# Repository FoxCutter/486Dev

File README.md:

# 486Dev
Repo for the 486 breadboard computer project

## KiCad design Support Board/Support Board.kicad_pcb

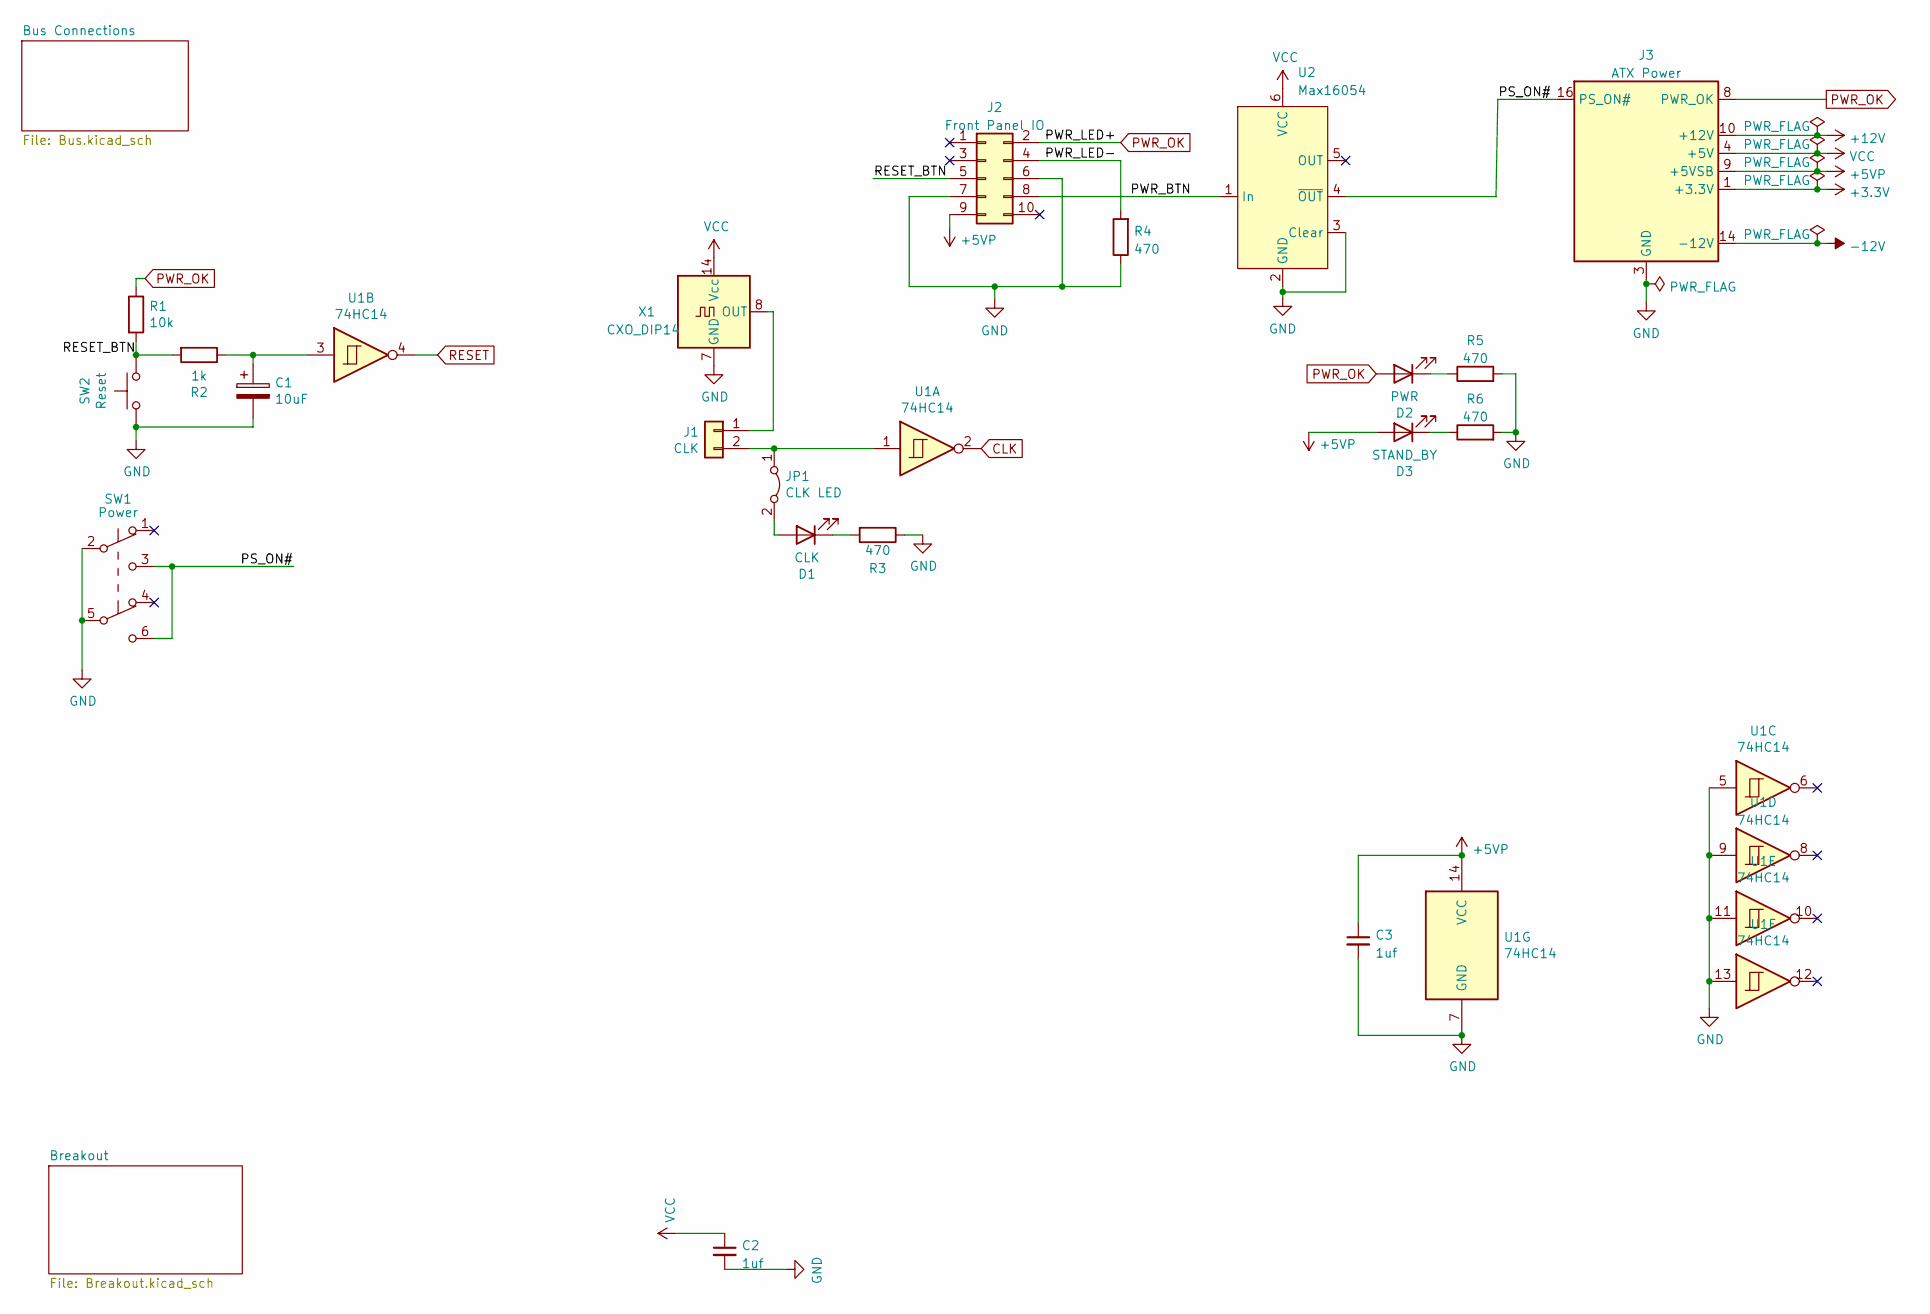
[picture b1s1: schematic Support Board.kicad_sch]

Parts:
C1: 10uF; CP_Radial_D5.0mm_P2.50mm
C2, C3: 1uf; C_0805_2012Metric_Pad1.18x1.45mm_HandSolder
D1: CLK; LED_0805_2012Metric_Pad1.15x1.40mm_HandSolder
D2: PWR; LED_0805_2012Metric_Pad1.15x1.40mm_HandSolder
D3: STAND_BY; LED_0805_2012Metric_Pad1.15x1.40mm_HandSolder
J1: CLK; PinHeader_1x02_P2.54mm_Vertical
J2: Front Panel IO; PinHeader_2x05_P2.54mm_Vertical
J3: ATX Power; Molex_Mini-Fit_Jr_5566-24A_2x12_P4.20mm_Vertical
JP1: CLK LED; PinHeader_1x02_P2.54mm_Vertical
R1: 10k; R_0805_2012Metric_Pad1.20x1.40mm_HandSolder
R2: 1k; R_0805_2012Metric_Pad1.20x1.40mm_HandSolder
R3, R4, R5, R6: 470; R_0805_2012Metric_Pad1.20x1.40mm_HandSolder
SW1: Power; 7mm x 7mm Tactile Switch
SW2: Reset; SW_PUSH_6mm
U1: 74HC14; SO-14_5.3x10.2mm_P1.27mm
U2: Max16054; TSOT-23-6
X1: CXO_DIP14; Oscillator_DIP-14

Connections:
+3.3V: J3.1 (+3.3V), J3.2 (+3.3V), J3.12 (+3.3V), J3.13 (+3.3V); also elsewhere on the board
+5VP: C3.1, D3.2 (A), J2.9, J3.9 (+5VSB), U1.14 (VCC); also elsewhere on the board
+12V: J3.10 (+12V), J3.11 (+12V); also elsewhere on the board
-12V: J3.14 (-12V); also elsewhere on the board
/PS_ON#: J3.16 (PS_ON#), SW1.3 (C), SW1.6 (C), U2.4 (~OUT)
/PWR_BTN: J2.8, U2.1 (In)
/PWR_LED-: J2.4, R4.2
/RESET_BTN: J2.5, R1.2, R2.2, SW2.2
CLK: U1.2; also elsewhere on the board
GND: C1.2, C2.2, C3.2, J2.6, J2.7, J3.3 (GND), J3.5 (GND), J3.7 (GND), J3.15 (GND), J3.17 (GND), J3.18 (GND), J3.19 (GND), J3.24 (GND), R3.1, R4.1, R5.2, R6.2, SW1.2 (B), SW1.5 (B), SW2.1, U1.5, U1.7 (GND), U1.9, U1.11, U1.13, U2.2 (GND), U2.3 (Clear), X1.7 (GND); also elsewhere on the board
unnamed: C1.1, R2.1, U1.3
unnamed: D1.1 (K), R3.2
unnamed: D1.2 (A), JP1.2 (B)
unnamed: D2.1 (K), R5.1
unnamed: D3.1 (K), R6.1
unnamed: J1.1, X1.8 (OUT)
unnamed: J1.2, JP1.1 (A), U1.1
PWR_OK: D2.2 (A), J2.2, J3.8 (PWR_OK), R1.1; also elsewhere on the board
RESET: U1.4; also elsewhere on the board
VCC: C2.1, J3.4 (+5V), J3.6 (+5V), J3.21 (+5V), J3.22 (+5V), J3.23 (+5V), U2.6 (VCC), X1.14 (Vcc); also elsewhere on the board

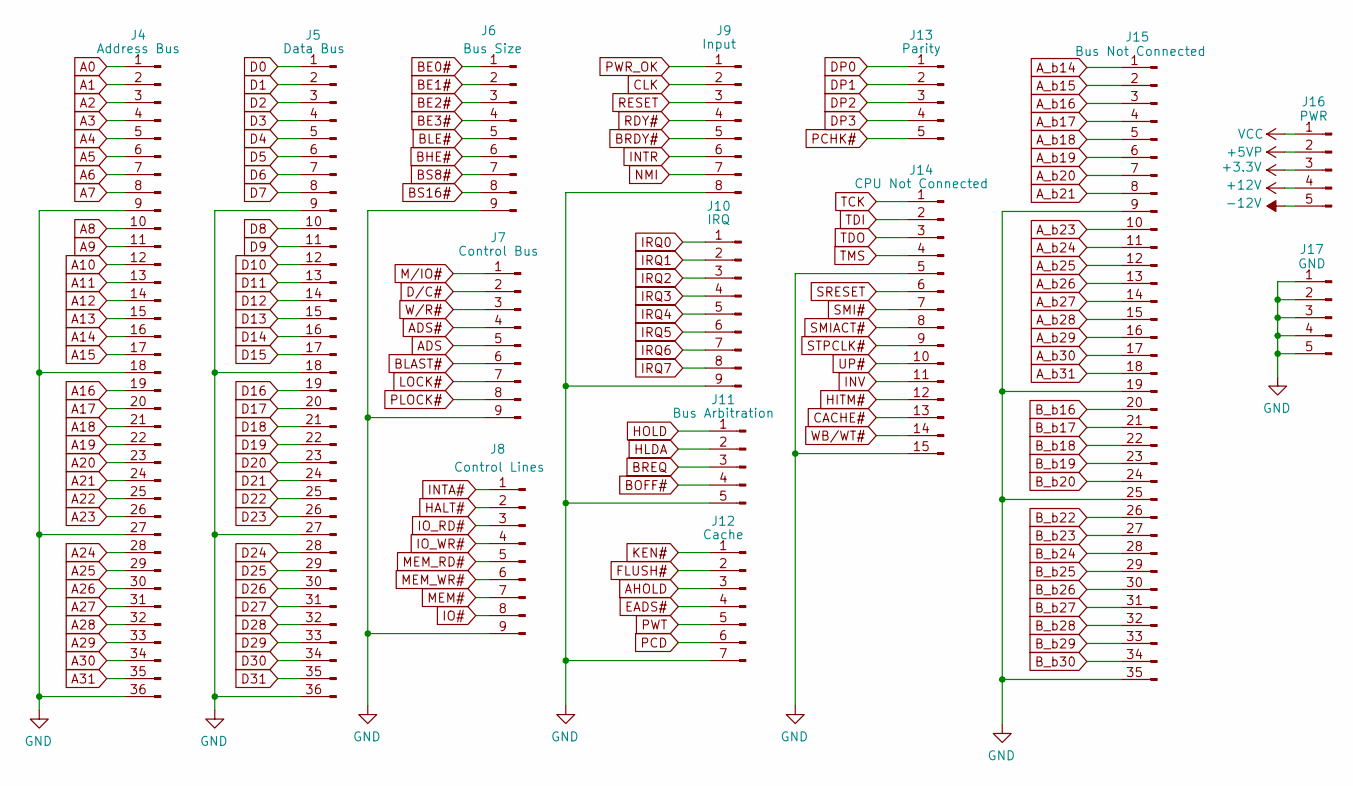
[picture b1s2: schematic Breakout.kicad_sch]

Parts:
J4: Address Bus; PinHeader_1x36_P2.54mm_Vertical
J5: Data Bus; PinHeader_1x36_P2.54mm_Vertical
J6: Bus Size; PinHeader_1x09_P2.54mm_Vertical
J7: Control Bus; PinHeader_1x09_P2.54mm_Vertical
J8: Control Lines; PinHeader_1x09_P2.54mm_Vertical
J9: Input; PinHeader_1x08_P2.54mm_Vertical
J10: IRQ; PinHeader_1x09_P2.54mm_Vertical
J11: Bus Arbitration; PinHeader_1x05_P2.54mm_Vertical
J12: Cache; PinHeader_1x07_P2.54mm_Vertical
J13: Parity; PinHeader_1x05_P2.54mm_Vertical
J14: CPU Not Connected; PinHeader_1x15_P2.54mm_Vertical
J15: Bus Not Connected; PinHeader_1x35_P2.54mm_Vertical
J16: PWR; PinHeader_1x05_P2.54mm_Vertical
J17: GND; PinHeader_1x05_P2.54mm_Vertical

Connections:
+3.3V: J16.3; also elsewhere on the board
+5VP: J16.2; also elsewhere on the board
+12V: J16.4; also elsewhere on the board
-12V: J16.5; also elsewhere on the board
A0: J4.1; also elsewhere on the board
A1: J4.2; also elsewhere on the board
A2: J4.3; also elsewhere on the board
A3: J4.4; also elsewhere on the board
A4: J4.5; also elsewhere on the board
A5: J4.6; also elsewhere on the board
A6: J4.7; also elsewhere on the board
A7: J4.8; also elsewhere on the board
A8: J4.10; also elsewhere on the board
A9: J4.11; also elsewhere on the board
A10: J4.12; also elsewhere on the board
A11: J4.13; also elsewhere on the board
A12: J4.14; also elsewhere on the board
A13: J4.15; also elsewhere on the board
A14: J4.16; also elsewhere on the board
A15: J4.17; also elsewhere on the board
A16: J4.19; also elsewhere on the board
A17: J4.20; also elsewhere on the board
A18: J4.21; also elsewhere on the board
A19: J4.22; also elsewhere on the board
A20: J4.23; also elsewhere on the board
A21: J4.24; also elsewhere on the board
A22: J4.25; also elsewhere on the board
A23: J4.26; also elsewhere on the board
A24: J4.28; also elsewhere on the board
A25: J4.29; also elsewhere on the board
A26: J4.30; also elsewhere on the board
A27: J4.31; also elsewhere on the board
A28: J4.32; also elsewhere on the board
A29: J4.33; also elsewhere on the board
A30: J4.34; also elsewhere on the board
A31: J4.35; also elsewhere on the board
ADS: J7.5; also elsewhere on the board
ADS#: J7.4; also elsewhere on the board
AHOLD: J12.3; also elsewhere on the board
A_b14: J15.1; also elsewhere on the board
A_b15: J15.2; also elsewhere on the board
A_b16: J15.3; also elsewhere on the board
A_b17: J15.4; also elsewhere on the board
A_b18: J15.5; also elsewhere on the board
A_b19: J15.6; also elsewhere on the board
A_b20: J15.7; also elsewhere on the board
A_b21: J15.8; also elsewhere on the board
A_b23: J15.10; also elsewhere on the board
A_b24: J15.11; also elsewhere on the board
A_b25: J15.12; also elsewhere on the board
A_b26: J15.13; also elsewhere on the board
A_b27: J15.14; also elsewhere on the board
A_b28: J15.15; also elsewhere on the board
A_b29: J15.16; also elsewhere on the board
A_b30: J15.17; also elsewhere on the board
A_b31: J15.18; also elsewhere on the board
BE0#: J6.1; also elsewhere on the board
BE1#: J6.2; also elsewhere on the board
BE2#: J6.3; also elsewhere on the board
BE3#: J6.4; also elsewhere on the board
BHE#: J6.6; also elsewhere on the board
BLAST#: J7.6; also elsewhere on the board
BLE#: J6.5; also elsewhere on the board
BOFF#: J11.4; also elsewhere on the board
BRDY#: J9.5; also elsewhere on the board
BREQ: J11.3; also elsewhere on the board
BS8#: J6.7; also elsewhere on the board
BS16#: J6.8; also elsewhere on the board
B_b16: J15.20; also elsewhere on the board
B_b17: J15.21; also elsewhere on the board
B_b18: J15.22; also elsewhere on the board
B_b19: J15.23; also elsewhere on the board
B_b20: J15.24; also elsewhere on the board
B_b22: J15.26; also elsewhere on the board
B_b23: J15.27; also elsewhere on the board
B_b24: J15.28; also elsewhere on the board
B_b25: J15.29; also elsewhere on the board
B_b26: J15.30; also elsewhere on the board
B_b27: J15.31; also elsewhere on the board
B_b28: J15.32; also elsewhere on the board
B_b29: J15.33; also elsewhere on the board
B_b30: J15.34; also elsewhere on the board
CACHE#: J14.13; also elsewhere on the board
CLK: J9.2; also elsewhere on the board
D0: J5.1; also elsewhere on the board
D1: J5.2; also elsewhere on the board
D2: J5.3; also elsewhere on the board
D3: J5.4; also elsewhere on the board
D4: J5.5; also elsewhere on the board
D5: J5.6; also elsewhere on the board
D6: J5.7; also elsewhere on the board
D7: J5.8; also elsewhere on the board
D8: J5.10; also elsewhere on the board
D9: J5.11; also elsewhere on the board
D10: J5.12; also elsewhere on the board
D11: J5.13; also elsewhere on the board
D12: J5.14; also elsewhere on the board
D13: J5.15; also elsewhere on the board
D14: J5.16; also elsewhere on the board
D15: J5.17; also elsewhere on the board
D16: J5.19; also elsewhere on the board
D17: J5.20; also elsewhere on the board
D18: J5.21; also elsewhere on the board
D19: J5.22; also elsewhere on the board
D20: J5.23; also elsewhere on the board
D21: J5.24; also elsewhere on the board
D22: J5.25; also elsewhere on the board
D23: J5.26; also elsewhere on the board
D24: J5.28; also elsewhere on the board
D25: J5.29; also elsewhere on the board
D26: J5.30; also elsewhere on the board
D27: J5.31; also elsewhere on the board
D28: J5.32; also elsewhere on the board
D29: J5.33; also elsewhere on the board
D30: J5.34; also elsewhere on the board
D31: J5.35; also elsewhere on the board
DP0: J13.1; also elsewhere on the board
DP1: J13.2; also elsewhere on the board
DP2: J13.3; also elsewhere on the board
DP3: J13.4; also elsewhere on the board
D/C#: J7.2; also elsewhere on the board
EADS#: J12.4; also elsewhere on the board
FLUSH#: J12.2; also elsewhere on the board
GND: J4.9, J4.18, J4.27, J4.36, J5.9, J5.18, J5.27, J5.36, J6.9, J7.9, J8.9, J9.8, J10.9, J11.5, J12.7, J14.5, J14.15, J15.9, J15.19, J15.25, J15.35, J17.1, J17.2, J17.3, J17.4, J17.5; also elsewhere on the board
HALT#: J8.2; also elsewhere on the board
HITM#: J14.12; also elsewhere on the board
HLDA: J11.2; also elsewhere on the board
HOLD: J11.1; also elsewhere on the board
INTA#: J8.1; also elsewhere on the board
INTR: J9.6; also elsewhere on the board
INV: J14.11; also elsewhere on the board
IO#: J8.8; also elsewhere on the board
IO_RD#: J8.3; also elsewhere on the board
IO_WR#: J8.4; also elsewhere on the board
IRQ0: J10.1; also elsewhere on the board
IRQ1: J10.2; also elsewhere on the board
IRQ2: J10.3; also elsewhere on the board
IRQ3: J10.4; also elsewhere on the board
IRQ4: J10.5; also elsewhere on the board
IRQ5: J10.6; also elsewhere on the board
IRQ6: J10.7; also elsewhere on the board
IRQ7: J10.8; also elsewhere on the board
KEN#: J12.1; also elsewhere on the board
LOCK#: J7.7; also elsewhere on the board
MEM#: J8.7; also elsewhere on the board
MEM_RD#: J8.5; also elsewhere on the board
MEM_WR#: J8.6; also elsewhere on the board
M/IO#: J7.1; also elsewhere on the board
NMI: J9.7; also elsewhere on the board
PCD: J12.6; also elsewhere on the board
PCHK#: J13.5; also elsewhere on the board
PLOCK#: J7.8; also elsewhere on the board
PWR_OK: J9.1; also elsewhere on the board
PWT: J12.5; also elsewhere on the board
RDY#: J9.4; also elsewhere on the board
RESET: J9.3; also elsewhere on the board
SMI#: J14.7; also elsewhere on the board
SMIACT#: J14.8; also elsewhere on the board
SRESET: J14.6; also elsewhere on the board
STPCLK#: J14.9; also elsewhere on the board
TCK: J14.1; also elsewhere on the board
TDI: J14.2; also elsewhere on the board
TDO: J14.3; also elsewhere on the board
TMS: J14.4; also elsewhere on the board
UP#: J14.10; also elsewhere on the board
VCC: J16.1; also elsewhere on the board
WB/WT#: J14.14; also elsewhere on the board
W/R#: J7.3; also elsewhere on the board

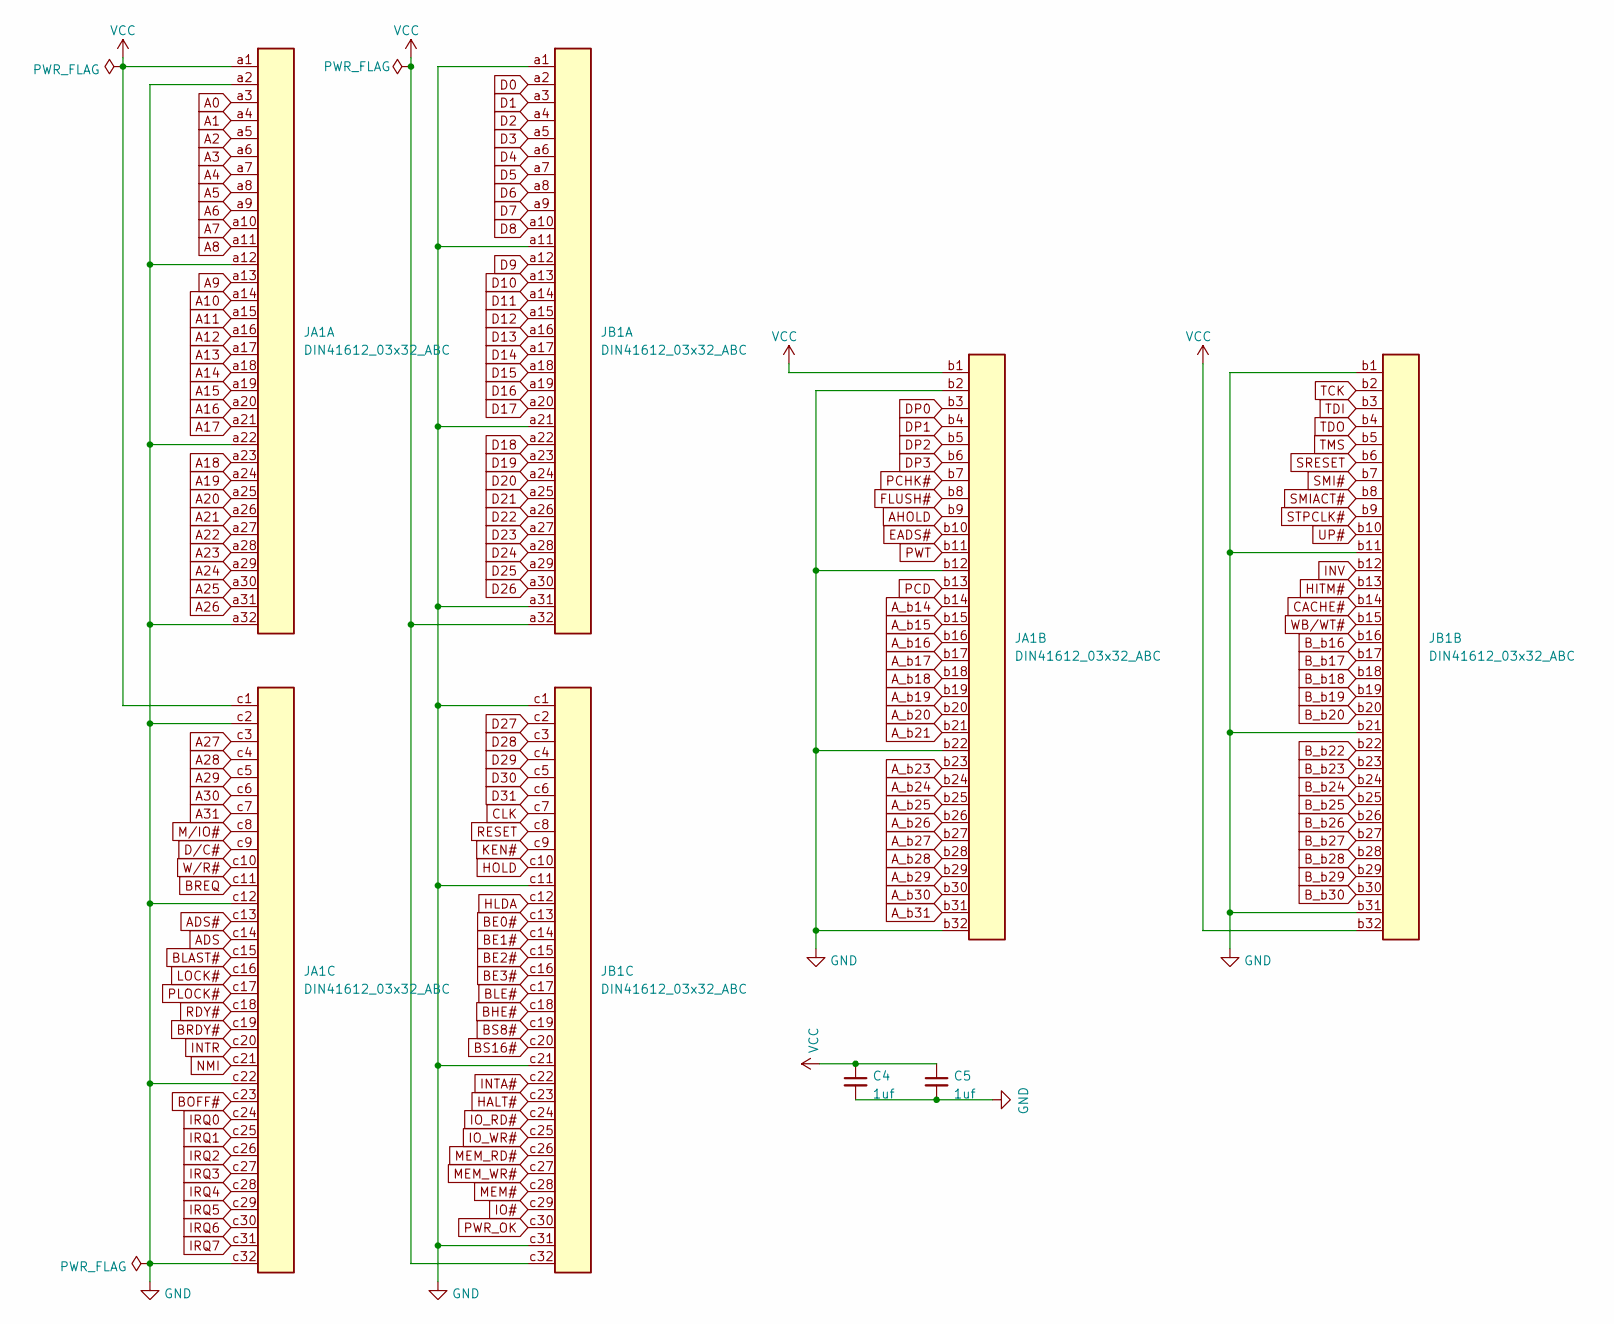
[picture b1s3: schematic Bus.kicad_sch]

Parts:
C4, C5: 1uf; C_0805_2012Metric_Pad1.18x1.45mm_HandSolder
JA1: DIN41612_03x32_ABC; DIN41612_R_3x32_Male_Horizontal_THT
JB1: DIN41612_03x32_ABC; DIN41612_R_3x32_Male_Horizontal_THT

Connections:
A0: JA1.a3; also elsewhere on the board
A1: JA1.a4; also elsewhere on the board
A2: JA1.a5; also elsewhere on the board
A3: JA1.a6; also elsewhere on the board
A4: JA1.a7; also elsewhere on the board
A5: JA1.a8; also elsewhere on the board
A6: JA1.a9; also elsewhere on the board
A7: JA1.a10; also elsewhere on the board
A8: JA1.a11; also elsewhere on the board
A9: JA1.a13; also elsewhere on the board
A10: JA1.a14; also elsewhere on the board
A11: JA1.a15; also elsewhere on the board
A12: JA1.a16; also elsewhere on the board
A13: JA1.a17; also elsewhere on the board
A14: JA1.a18; also elsewhere on the board
A15: JA1.a19; also elsewhere on the board
A16: JA1.a20; also elsewhere on the board
A17: JA1.a21; also elsewhere on the board
A18: JA1.a23; also elsewhere on the board
A19: JA1.a24; also elsewhere on the board
A20: JA1.a25; also elsewhere on the board
A21: JA1.a26; also elsewhere on the board
A22: JA1.a27; also elsewhere on the board
A23: JA1.a28; also elsewhere on the board
A24: JA1.a29; also elsewhere on the board
A25: JA1.a30; also elsewhere on the board
A26: JA1.a31; also elsewhere on the board
A27: JA1.c3; also elsewhere on the board
A28: JA1.c4; also elsewhere on the board
A29: JA1.c5; also elsewhere on the board
A30: JA1.c6; also elsewhere on the board
A31: JA1.c7; also elsewhere on the board
ADS: JA1.c14; also elsewhere on the board
ADS#: JA1.c13; also elsewhere on the board
AHOLD: JA1.b9; also elsewhere on the board
A_b14: JA1.b14; also elsewhere on the board
A_b15: JA1.b15; also elsewhere on the board
A_b16: JA1.b16; also elsewhere on the board
A_b17: JA1.b17; also elsewhere on the board
A_b18: JA1.b18; also elsewhere on the board
A_b19: JA1.b19; also elsewhere on the board
A_b20: JA1.b20; also elsewhere on the board
A_b21: JA1.b21; also elsewhere on the board
A_b23: JA1.b23; also elsewhere on the board
A_b24: JA1.b24; also elsewhere on the board
A_b25: JA1.b25; also elsewhere on the board
A_b26: JA1.b26; also elsewhere on the board
A_b27: JA1.b27; also elsewhere on the board
A_b28: JA1.b28; also elsewhere on the board
A_b29: JA1.b29; also elsewhere on the board
A_b30: JA1.b30; also elsewhere on the board
A_b31: JA1.b31; also elsewhere on the board
BE0#: JB1.c13; also elsewhere on the board
BE1#: JB1.c14; also elsewhere on the board
BE2#: JB1.c15; also elsewhere on the board
BE3#: JB1.c16; also elsewhere on the board
BHE#: JB1.c18; also elsewhere on the board
BLAST#: JA1.c15; also elsewhere on the board
BLE#: JB1.c17; also elsewhere on the board
BOFF#: JA1.c23; also elsewhere on the board
BRDY#: JA1.c19; also elsewhere on the board
BREQ: JA1.c11; also elsewhere on the board
BS8#: JB1.c19; also elsewhere on the board
BS16#: JB1.c20; also elsewhere on the board
B_b16: JB1.b16; also elsewhere on the board
B_b17: JB1.b17; also elsewhere on the board
B_b18: JB1.b18; also elsewhere on the board
B_b19: JB1.b19; also elsewhere on the board
B_b20: JB1.b20; also elsewhere on the board
B_b22: JB1.b22; also elsewhere on the board
B_b23: JB1.b23; also elsewhere on the board
B_b24: JB1.b24; also elsewhere on the board
B_b25: JB1.b25; also elsewhere on the board
B_b26: JB1.b26; also elsewhere on the board
B_b27: JB1.b27; also elsewhere on the board
B_b28: JB1.b28; also elsewhere on the board
B_b29: JB1.b29; also elsewhere on the board
B_b30: JB1.b30; also elsewhere on the board
CACHE#: JB1.b14; also elsewhere on the board
CLK: JB1.c7; also elsewhere on the board
D0: JB1.a2; also elsewhere on the board
D1: JB1.a3; also elsewhere on the board
D2: JB1.a4; also elsewhere on the board
D3: JB1.a5; also elsewhere on the board
D4: JB1.a6; also elsewhere on the board
D5: JB1.a7; also elsewhere on the board
D6: JB1.a8; also elsewhere on the board
D7: JB1.a9; also elsewhere on the board
D8: JB1.a10; also elsewhere on the board
D9: JB1.a12; also elsewhere on the board
D10: JB1.a13; also elsewhere on the board
D11: JB1.a14; also elsewhere on the board
D12: JB1.a15; also elsewhere on the board
D13: JB1.a16; also elsewhere on the board
D14: JB1.a17; also elsewhere on the board
D15: JB1.a18; also elsewhere on the board
D16: JB1.a19; also elsewhere on the board
D17: JB1.a20; also elsewhere on the board
D18: JB1.a22; also elsewhere on the board
D19: JB1.a23; also elsewhere on the board
D20: JB1.a24; also elsewhere on the board
D21: JB1.a25; also elsewhere on the board
D22: JB1.a26; also elsewhere on the board
D23: JB1.a27; also elsewhere on the board
D24: JB1.a28; also elsewhere on the board
D25: JB1.a29; also elsewhere on the board
D26: JB1.a30; also elsewhere on the board
D27: JB1.c2; also elsewhere on the board
D28: JB1.c3; also elsewhere on the board
D29: JB1.c4; also elsewhere on the board
D30: JB1.c5; also elsewhere on the board
D31: JB1.c6; also elsewhere on the board
DP0: JA1.b3; also elsewhere on the board
DP1: JA1.b4; also elsewhere on the board
DP2: JA1.b5; also elsewhere on the board
DP3: JA1.b6; also elsewhere on the board
D/C#: JA1.c9; also elsewhere on the board
EADS#: JA1.b10; also elsewhere on the board
FLUSH#: JA1.b8; also elsewhere on the board
GND: C4.2, C5.2, JA1.a2, JA1.a12, JA1.a22, JA1.a32, JA1.b2, JA1.b12, JA1.b22, JA1.b32, JA1.c2, JA1.c12, JA1.c22, JA1.c32, JB1.a1, JB1.a11, JB1.a21, JB1.a31, JB1.b1, JB1.b11, JB1.b21, JB1.b31, JB1.c1, JB1.c11, JB1.c21, JB1.c31; also elsewhere on the board
HALT#: JB1.c23; also elsewhere on the board
HITM#: JB1.b13; also elsewhere on the board
HLDA: JB1.c12; also elsewhere on the board
HOLD: JB1.c10; also elsewhere on the board
INTA#: JB1.c22; also elsewhere on the board
INTR: JA1.c20; also elsewhere on the board
INV: JB1.b12; also elsewhere on the board
IO#: JB1.c29; also elsewhere on the board
IO_RD#: JB1.c24; also elsewhere on the board
IO_WR#: JB1.c25; also elsewhere on the board
IRQ0: JA1.c24; also elsewhere on the board
IRQ1: JA1.c25; also elsewhere on the board
IRQ2: JA1.c26; also elsewhere on the board
IRQ3: JA1.c27; also elsewhere on the board
IRQ4: JA1.c28; also elsewhere on the board
IRQ5: JA1.c29; also elsewhere on the board
IRQ6: JA1.c30; also elsewhere on the board
IRQ7: JA1.c31; also elsewhere on the board
KEN#: JB1.c9; also elsewhere on the board
LOCK#: JA1.c16; also elsewhere on the board
MEM#: JB1.c28; also elsewhere on the board
MEM_RD#: JB1.c26; also elsewhere on the board
MEM_WR#: JB1.c27; also elsewhere on the board
M/IO#: JA1.c8; also elsewhere on the board
NMI: JA1.c21; also elsewhere on the board
PCD: JA1.b13; also elsewhere on the board
PCHK#: JA1.b7; also elsewhere on the board
PLOCK#: JA1.c17; also elsewhere on the board
PWR_OK: JB1.c30; also elsewhere on the board
PWT: JA1.b11; also elsewhere on the board
RDY#: JA1.c18; also elsewhere on the board
RESET: JB1.c8; also elsewhere on the board
SMI#: JB1.b7; also elsewhere on the board
SMIACT#: JB1.b8; also elsewhere on the board
SRESET: JB1.b6; also elsewhere on the board
STPCLK#: JB1.b9; also elsewhere on the board
TCK: JB1.b2; also elsewhere on the board
TDI: JB1.b3; also elsewhere on the board
TDO: JB1.b4; also elsewhere on the board
TMS: JB1.b5; also elsewhere on the board
UP#: JB1.b10; also elsewhere on the board
VCC: C4.1, C5.1, JA1.a1, JA1.b1, JA1.c1, JB1.a32, JB1.b32, JB1.c32; also elsewhere on the board
WB/WT#: JB1.b15; also elsewhere on the board
W/R#: JA1.c10; also elsewhere on the board

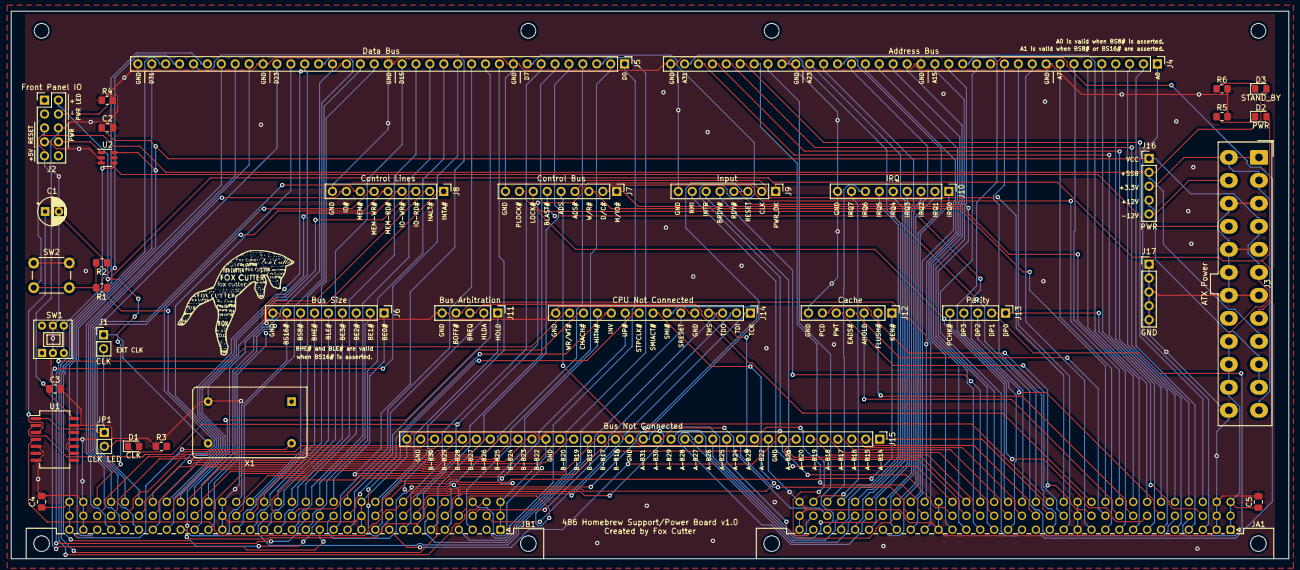
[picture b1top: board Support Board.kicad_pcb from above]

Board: 2 copper layers, 233.3 x 100.0 mm, 43 parts (0 on the bottom side), 179 nets.

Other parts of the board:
REF1, REF2, REF3, REF4: MountingHole_2.7mm_M2.5_ISO7380

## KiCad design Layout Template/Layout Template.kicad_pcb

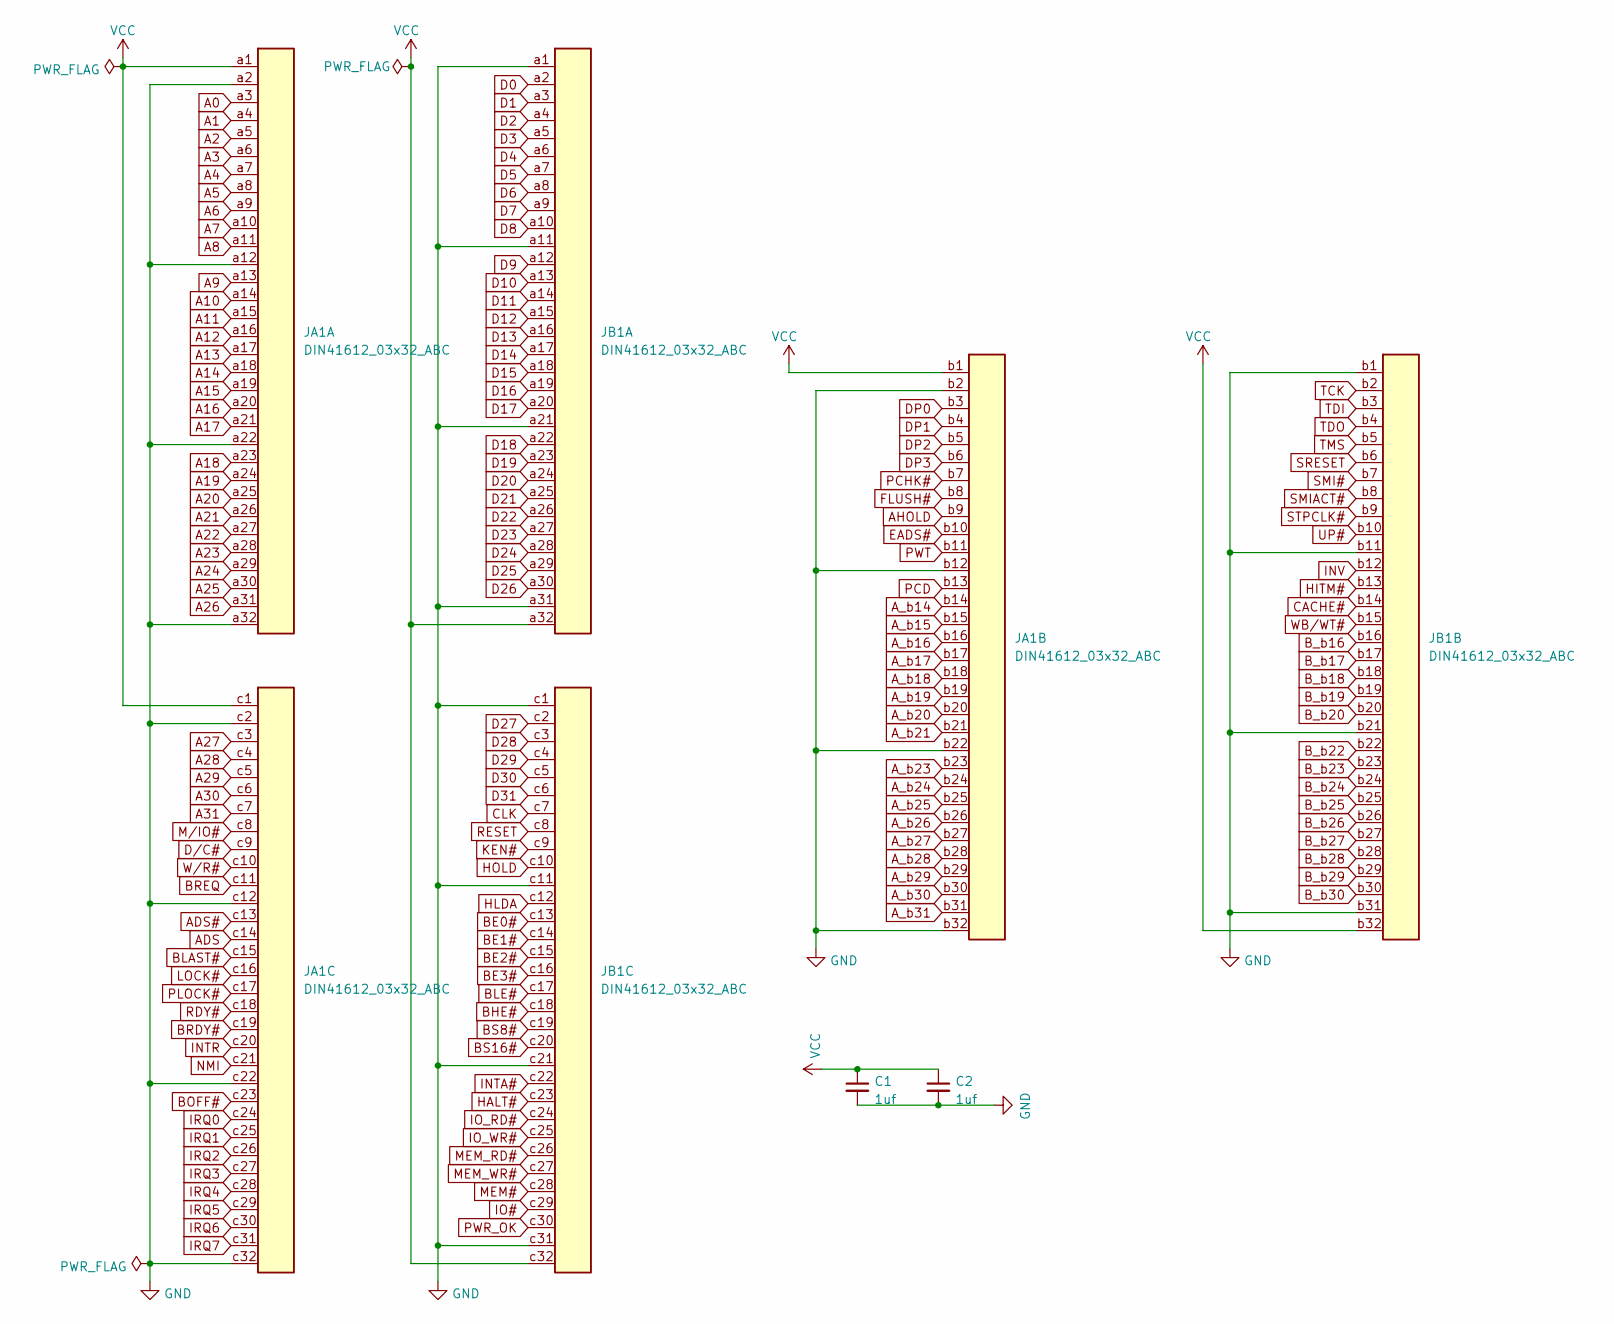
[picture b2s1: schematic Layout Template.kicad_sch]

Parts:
C1, C2: 1uf; C_Disc_D4.7mm_W2.5mm_P5.00mm
JA1: DIN41612_03x32_ABC; DIN41612_R_3x32_Male_Horizontal_THT
JB1: DIN41612_03x32_ABC; DIN41612_R_3x32_Male_Horizontal_THT

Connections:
A0: JA1.a3
A1: JA1.a4
A2: JA1.a5
A3: JA1.a6
A4: JA1.a7
A5: JA1.a8
A6: JA1.a9
A7: JA1.a10
A8: JA1.a11
A9: JA1.a13
A10: JA1.a14
A11: JA1.a15
A12: JA1.a16
A13: JA1.a17
A14: JA1.a18
A15: JA1.a19
A16: JA1.a20
A17: JA1.a21
A18: JA1.a23
A19: JA1.a24
A20: JA1.a25
A21: JA1.a26
A22: JA1.a27
A23: JA1.a28
A24: JA1.a29
A25: JA1.a30
A26: JA1.a31
A27: JA1.c3
A28: JA1.c4
A29: JA1.c5
A30: JA1.c6
A31: JA1.c7
ADS: JA1.c14
ADS#: JA1.c13
AHOLD: JA1.b9
A_b14: JA1.b14
A_b15: JA1.b15
A_b16: JA1.b16
A_b17: JA1.b17
A_b18: JA1.b18
A_b19: JA1.b19
A_b20: JA1.b20
A_b21: JA1.b21
A_b23: JA1.b23
A_b24: JA1.b24
A_b25: JA1.b25
A_b26: JA1.b26
A_b27: JA1.b27
A_b28: JA1.b28
A_b29: JA1.b29
A_b30: JA1.b30
A_b31: JA1.b31
BE0#: JB1.c13
BE1#: JB1.c14
BE2#: JB1.c15
BE3#: JB1.c16
BHE#: JB1.c18
BLAST#: JA1.c15
BLE#: JB1.c17
BOFF#: JA1.c23
BRDY#: JA1.c19
BREQ: JA1.c11
BS8#: JB1.c19
BS16#: JB1.c20
B_b16: JB1.b16
B_b17: JB1.b17
B_b18: JB1.b18
B_b19: JB1.b19
B_b20: JB1.b20
B_b22: JB1.b22
B_b23: JB1.b23
B_b24: JB1.b24
B_b25: JB1.b25
B_b26: JB1.b26
B_b27: JB1.b27
B_b28: JB1.b28
B_b29: JB1.b29
B_b30: JB1.b30
CACHE#: JB1.b14
CLK: JB1.c7
D0: JB1.a2
D1: JB1.a3
D2: JB1.a4
D3: JB1.a5
D4: JB1.a6
D5: JB1.a7
D6: JB1.a8
D7: JB1.a9
D8: JB1.a10
D9: JB1.a12
D10: JB1.a13
D11: JB1.a14
D12: JB1.a15
D13: JB1.a16
D14: JB1.a17
D15: JB1.a18
D16: JB1.a19
D17: JB1.a20
D18: JB1.a22
D19: JB1.a23
D20: JB1.a24
D21: JB1.a25
D22: JB1.a26
D23: JB1.a27
D24: JB1.a28
D25: JB1.a29
D26: JB1.a30
D27: JB1.c2
D28: JB1.c3
D29: JB1.c4
D30: JB1.c5
D31: JB1.c6
DP0: JA1.b3
DP1: JA1.b4
DP2: JA1.b5
DP3: JA1.b6
D/C#: JA1.c9
EADS#: JA1.b10
FLUSH#: JA1.b8
GND: C1.2, C2.2, JA1.a2, JA1.a12, JA1.a22, JA1.a32, JA1.b2, JA1.b12, JA1.b22, JA1.b32, JA1.c2, JA1.c12, JA1.c22, JA1.c32, JB1.a1, JB1.a11, JB1.a21, JB1.a31, JB1.b1, JB1.b11, JB1.b21, JB1.b31, JB1.c1, JB1.c11, JB1.c21, JB1.c31
HALT#: JB1.c23
HITM#: JB1.b13
HLDA: JB1.c12
HOLD: JB1.c10
INTA#: JB1.c22
INTR: JA1.c20
INV: JB1.b12
IO#: JB1.c29
IO_RD#: JB1.c24
IO_WR#: JB1.c25
IRQ0: JA1.c24
IRQ1: JA1.c25
IRQ2: JA1.c26
IRQ3: JA1.c27
IRQ4: JA1.c28
IRQ5: JA1.c29
IRQ6: JA1.c30
IRQ7: JA1.c31
KEN#: JB1.c9
LOCK#: JA1.c16
MEM#: JB1.c28
MEM_RD#: JB1.c26
MEM_WR#: JB1.c27
M/IO#: JA1.c8
NMI: JA1.c21
PCD: JA1.b13
PCHK#: JA1.b7
PLOCK#: JA1.c17
PWR_OK: JB1.c30
PWT: JA1.b11
RDY#: JA1.c18
RESET: JB1.c8
SMI#: JB1.b7
SMIACT#: JB1.b8
SRESET: JB1.b6
STPCLK#: JB1.b9
TCK: JB1.b2
TDI: JB1.b3
TDO: JB1.b4
TMS: JB1.b5
UP#: JB1.b10
VCC: C1.1, C2.1, JA1.a1, JA1.b1, JA1.c1, JB1.a32, JB1.b32, JB1.c32
WB/WT#: JB1.b15
W/R#: JA1.c10

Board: 2 copper layers, 8 parts (0 on the bottom side), 2 nets, no tracks yet.

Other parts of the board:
REF1, REF2, REF3, REF4: MountingHole_2.7mm_M2.5_ISO7380
